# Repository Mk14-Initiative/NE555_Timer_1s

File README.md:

# NE555_Timer_1s
NE555 Timer Platine mit USB-Anschluss Takt 1s

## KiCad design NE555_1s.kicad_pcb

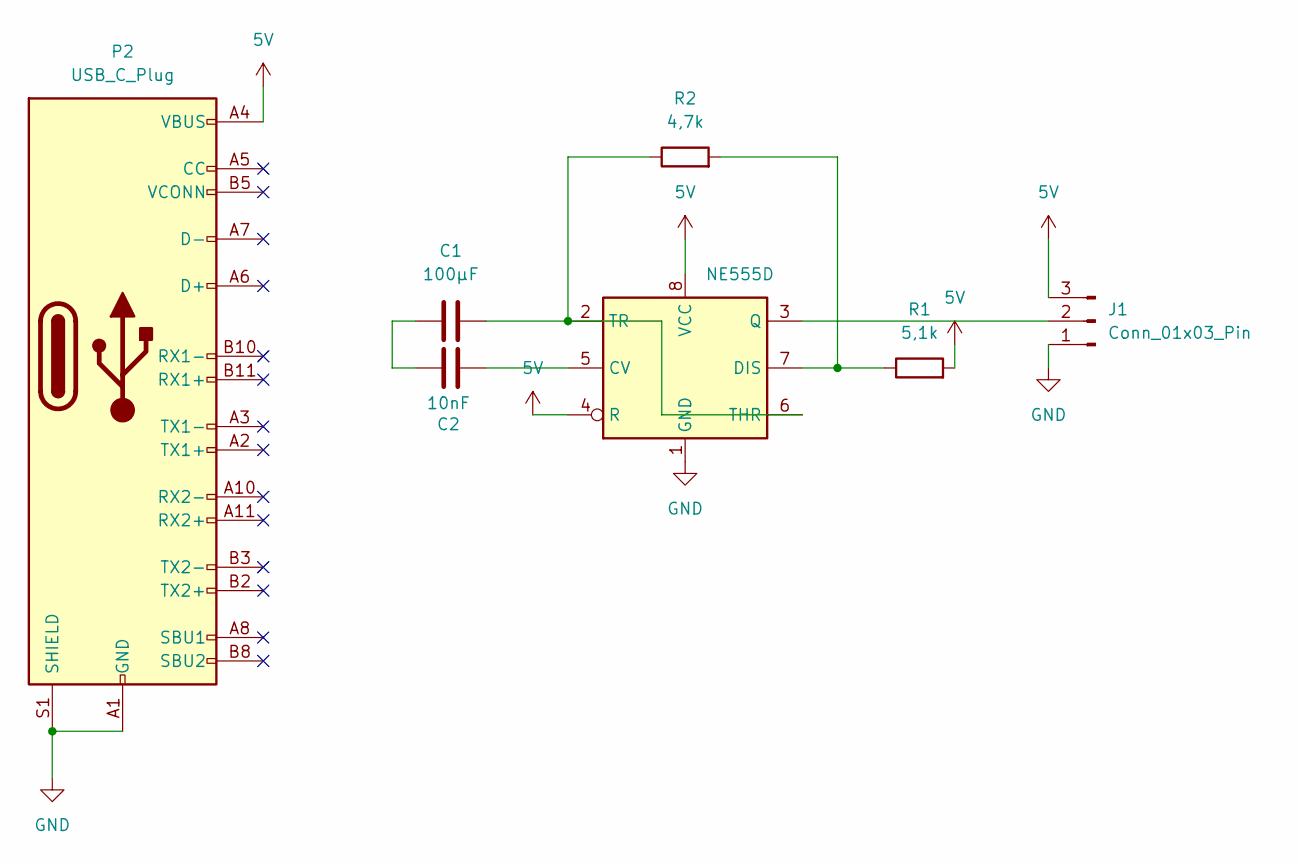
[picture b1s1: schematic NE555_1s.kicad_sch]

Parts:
C1: 100µF; C_0402_1005Metric
C2: 10nF; C_0402_1005Metric
J1: Conn_01x03_Pin; PinHeader_1x03_P1.00mm_Vertical
P2: USB_C_Plug; USB_C_Plug_ShenzhenJingTuoJin_918-118A2021Y40002_Vertical
R1: 5,1k; C_0402_1005Metric
R2: 4,7k; C_0402_1005Metric
U1: NE555D; SOIC-8_3.9x4.9mm_P1.27mm

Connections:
5V: J1.3, P2.A4 (VBUS), P2.A9 (VBUS), P2.B4 (VBUS), P2.B9 (VBUS), R1.2, U1.4 (R), U1.8 (VCC)
GND: J1.1, P2.A1 (GND), P2.A12 (GND), P2.B1 (GND), P2.B12 (GND), P2.S1 (SHIELD), U1.1 (GND)
unnamed: C1.1, C2.1
unnamed: J1.2, U1.3 (Q)
unnamed: C2.2, U1.5 (CV)
unnamed: R1.1, R2.2, U1.7 (DIS)
unnamed: C1.2, R2.1, U1.2 (TR), U1.6 (THR)

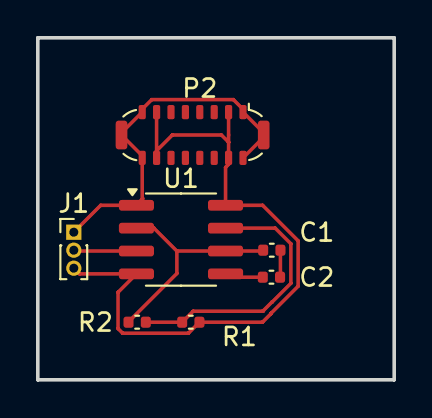
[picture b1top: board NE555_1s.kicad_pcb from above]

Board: 2 copper layers, 19.8 x 19.0 mm, 7 parts (0 on the bottom side), 7 nets.

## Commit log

2025-09-07 Add files via upload
    NE555 Timer Platine mit USB-Anschluss mit einem Takt von 1s
